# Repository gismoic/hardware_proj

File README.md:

These are all hardware projects I've done over the years, these designs taught me the basics of schematic design and PCB design. Here are some descriptions on each project

# FLAT_MOBO

This project was an attempt at creating a MP3 player design. This project made use of vs1053b codec chip that would take audio data streamed to it via a SPI connection and output a analog audio signal to speakers, the chip could also be used in conjunction with a external microcontroller for addiotional features. This project was a predessor to OTTO, a project that I would persue on later that shared a simiar theroy of operation.

# PIPBOY

this project was an attempt to redesign a gameboy with a Z80 computer instead of it's original hardware. This project also made use of a prototype gameboy emulator that I wanted to build to help me understand the hardware better. Here's a schematic that includes the computer's data and address bus connected to a sram package and a custom prehphrial that would act as a simulated cartridge.

# SD_P

A microSD card breakout board, a way to tinker with a SD card using hardware of my own desgin. A BOM was constructed detailing all parts, cost of each part, and links where to get them. Overall a very simple project.

# BB_PS (battery charger) [WIP]

A custom battery charger design that a uses a cc-cv circuit and a buck regulator for charging batteries. I hope to be able to add a microcontroller that monitors battery percentage and potentially other features. For now it is incomplete

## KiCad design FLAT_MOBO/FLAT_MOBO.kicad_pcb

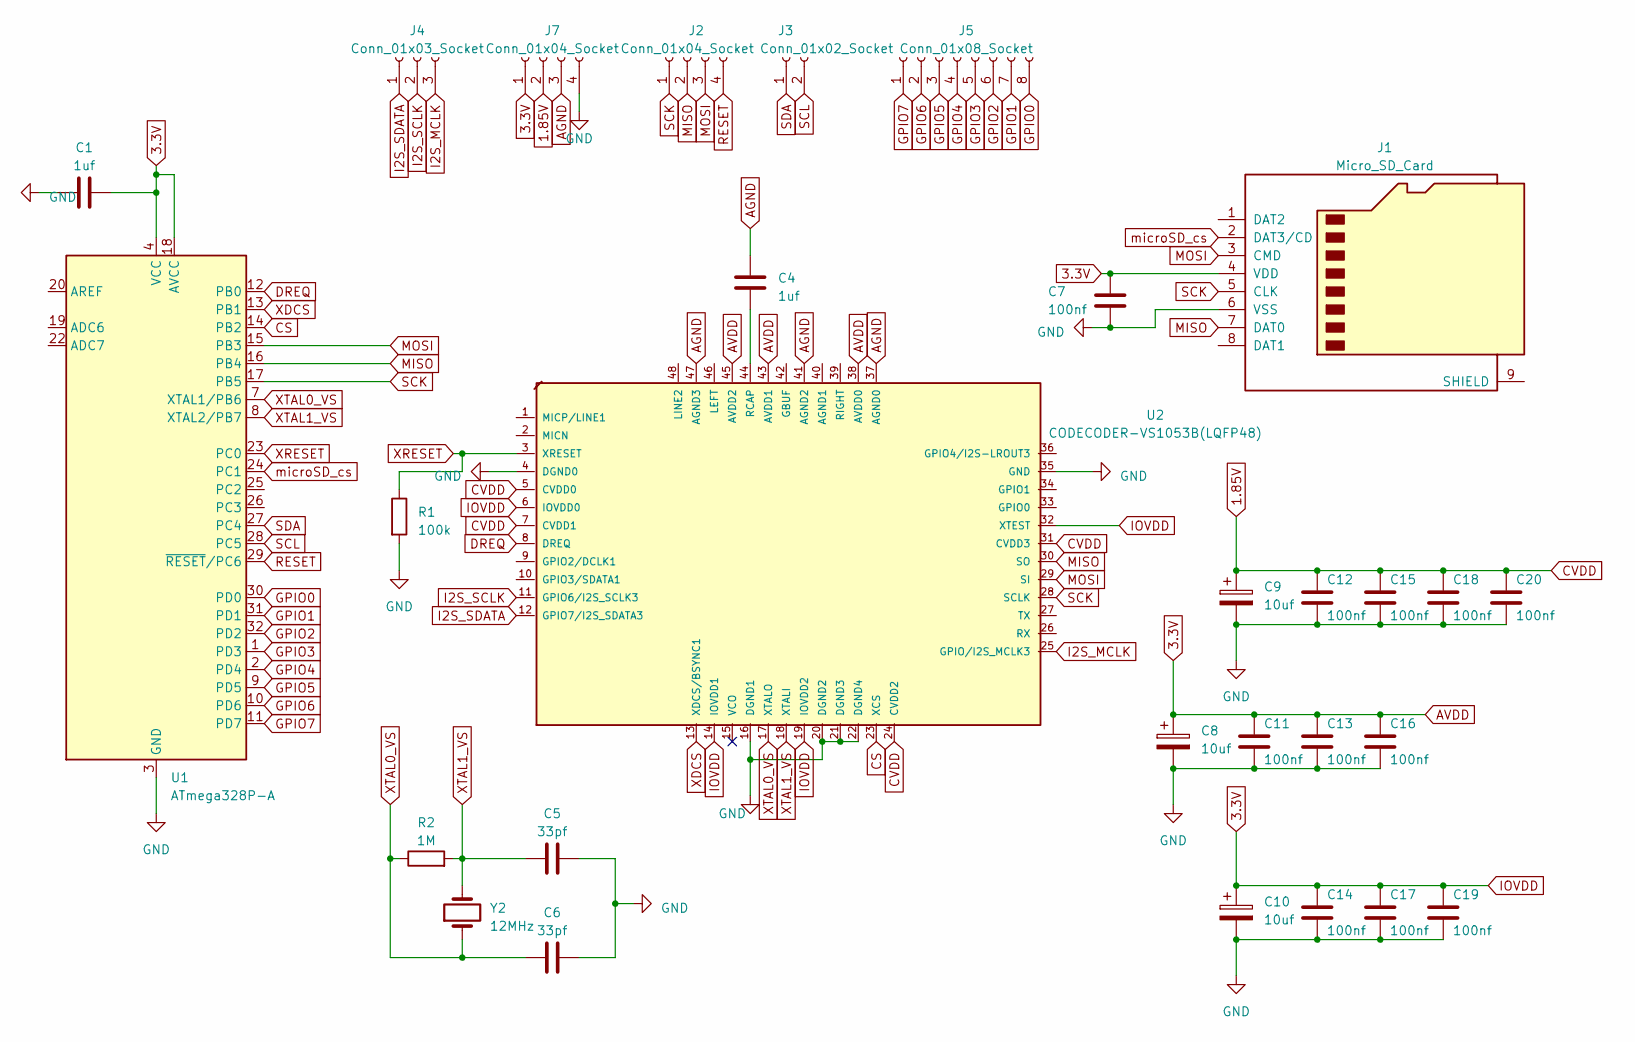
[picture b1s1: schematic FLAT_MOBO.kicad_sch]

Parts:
C1, C4: 1uf; C_0603_1608Metric_Pad1.08x0.95mm_HandSolder
C5, C6: 33pf; C_0603_1608Metric_Pad1.08x0.95mm_HandSolder
C7, C11, C12, C13, C14, C15, C16, C17, C18, C19, C20: 100nf; C_0603_1608Metric_Pad1.08x0.95mm_HandSolder
C8, C9, C10: 10uf; CP_Elec_4x3
J1: Micro_SD_Card; microSD_HC_Hirose_DM3D-SF
J2, J7: Conn_01x04_Socket; PinHeader_1x04_P1.27mm_Vertical
J3: Conn_01x02_Socket; PinHeader_1x02_P1.27mm_Vertical
J4: Conn_01x03_Socket; PinHeader_1x03_P1.27mm_Vertical
J5: Conn_01x08_Socket; PinHeader_1x08_P1.27mm_Vertical
R1: 100k; R_0603_1608Metric_Pad0.98x0.95mm_HandSolder
R2: 1M; R_0603_1608Metric_Pad0.98x0.95mm_HandSolder
U1: ATmega328P-A; TQFP-32_7x7mm_P0.8mm
U2: CODECODER-VS1053B(LQFP48); LQFP-48_7x7mm_P0.5mm; MPN VS1053B
Y2: 12MHz; Crystal_HC49-4H_Vertical

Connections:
1.85V: C9.1, C12.1, C15.1, C18.1, C20.1, J7.2, U2.5 (CVDD0), U2.7 (CVDD1), U2.24 (CVDD2), U2.31 (CVDD3)
3.3V: C1.2, C7.1, C8.1, C10.1, C11.1, C13.1, C14.1, C16.1, C17.1, C19.1, J1.4 (VDD), J7.1, U1.4 (VCC), U1.6 (VCC), U1.18 (AVCC), U2.6 (IOVDD0), U2.14 (IOVDD1), U2.19 (IOVDD2), U2.32 (XTEST), U2.38 (AVDD0), U2.43 (AVDD1), U2.45 (AVDD2)
AGND: C4.1, J7.3, U2.37 (AGND0), U2.41 (AGND2), U2.47 (AGND3)
CS: U1.14 (PB2), U2.23 (XCS)
DREQ: U1.12 (PB0), U2.8 (DREQ)
GND: C1.1, C5.2, C6.2, C7.2, C8.2, C9.2, C10.2, C11.2, C12.2, C13.2, C14.2, C15.2, C16.2, C17.2, C18.2, C19.2, C20.2, J1.6 (VSS), J7.4, R1.2, U1.3 (GND), U1.5 (GND), U1.21 (GND), U2.4 (DGND0), U2.16 (DGND1), U2.20 (DGND2), U2.21 (DGND3), U2.22 (DGND4), U2.35 (GND)
GPIO0: J5.8, U1.30 (PD0)
GPIO1: J5.7, U1.31 (PD1)
GPIO2: J5.6, U1.32 (PD2)
GPIO3: J5.5, U1.1 (PD3)
GPIO4: J5.4, U1.2 (PD4)
GPIO5: J5.3, U1.9 (PD5)
GPIO6: J5.2, U1.10 (PD6)
GPIO7: J5.1, U1.11 (PD7)
I2S_MCLK: J4.3, U2.25 (GPIO/I2S_MCLK3)
I2S_SCLK: J4.2, U2.11 (GPIO6/I2S_SCLK3)
I2S_SDATA: J4.1, U2.12 (GPIO7/I2S_SDATA3)
MISO: J1.7 (DAT0), J2.2, U1.16 (PB4), U2.30 (SO)
MOSI: J1.3 (CMD), J2.3, U1.15 (PB3), U2.29 (SI)
unnamed: C4.2, U2.44 (RCAP)
RESET: J2.4, U1.29 (~RESET/PC6)
SCK: J1.5 (CLK), J2.1, U1.17 (PB5), U2.28 (SCLK)
SCL: J3.2, U1.28 (PC5)
SDA: J3.1, U1.27 (PC4)
XDCS: U1.13 (PB1), U2.13 (XDCS/BSYNC1)
XRESET: R1.1, U1.23 (PC0), U2.3 (XRESET)
XTAL0_VS: C6.1, R2.1, U1.7 (XTAL1/PB6), U2.17 (XTALO), Y2.1
XTAL1_VS: C5.1, R2.2, U1.8 (XTAL2/PB7), U2.18 (XTALI), Y2.2
microSD_cs: J1.2 (DAT3/CD), U1.24 (PC1)
sCS: U1.25 (PC2)

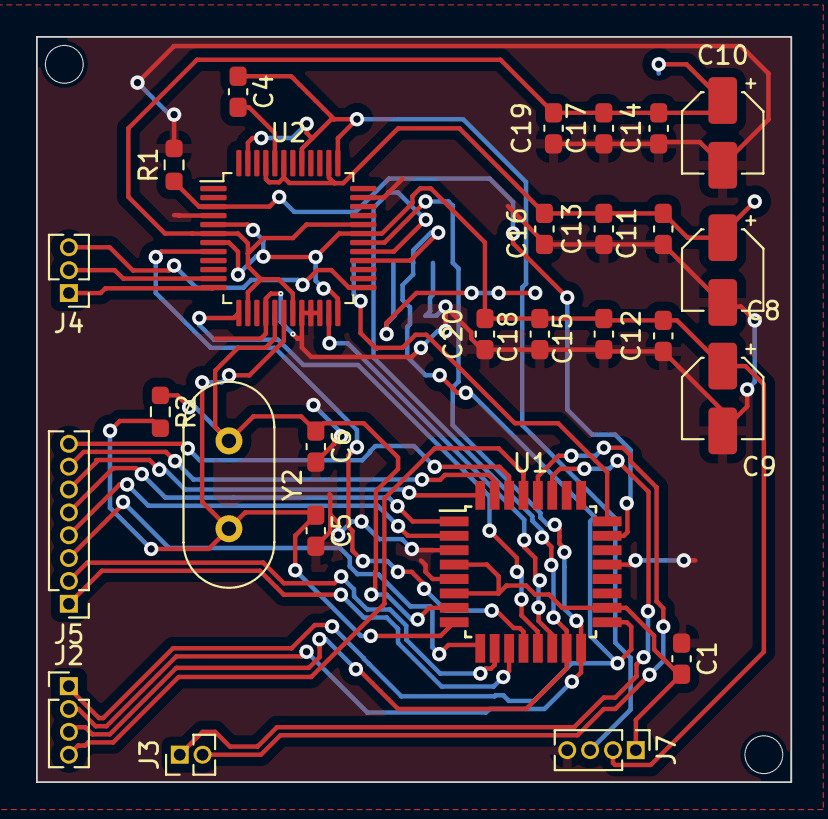
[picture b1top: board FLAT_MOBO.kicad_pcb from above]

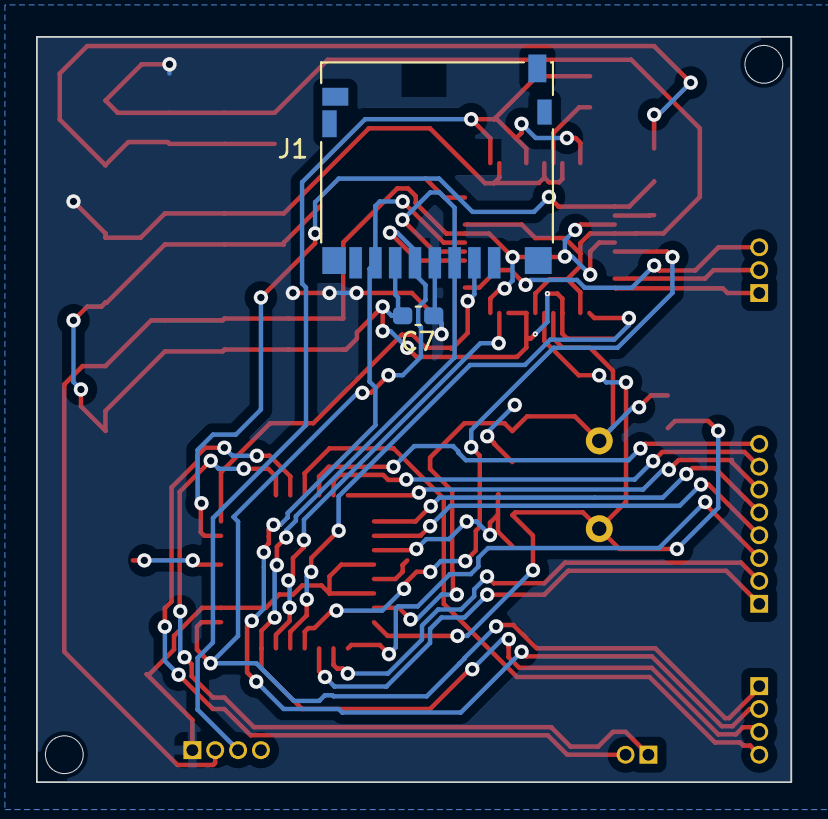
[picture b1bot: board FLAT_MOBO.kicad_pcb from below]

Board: 2 copper layers, 41.9 x 41.4 mm, 29 parts (2 on the bottom side), 29 nets.

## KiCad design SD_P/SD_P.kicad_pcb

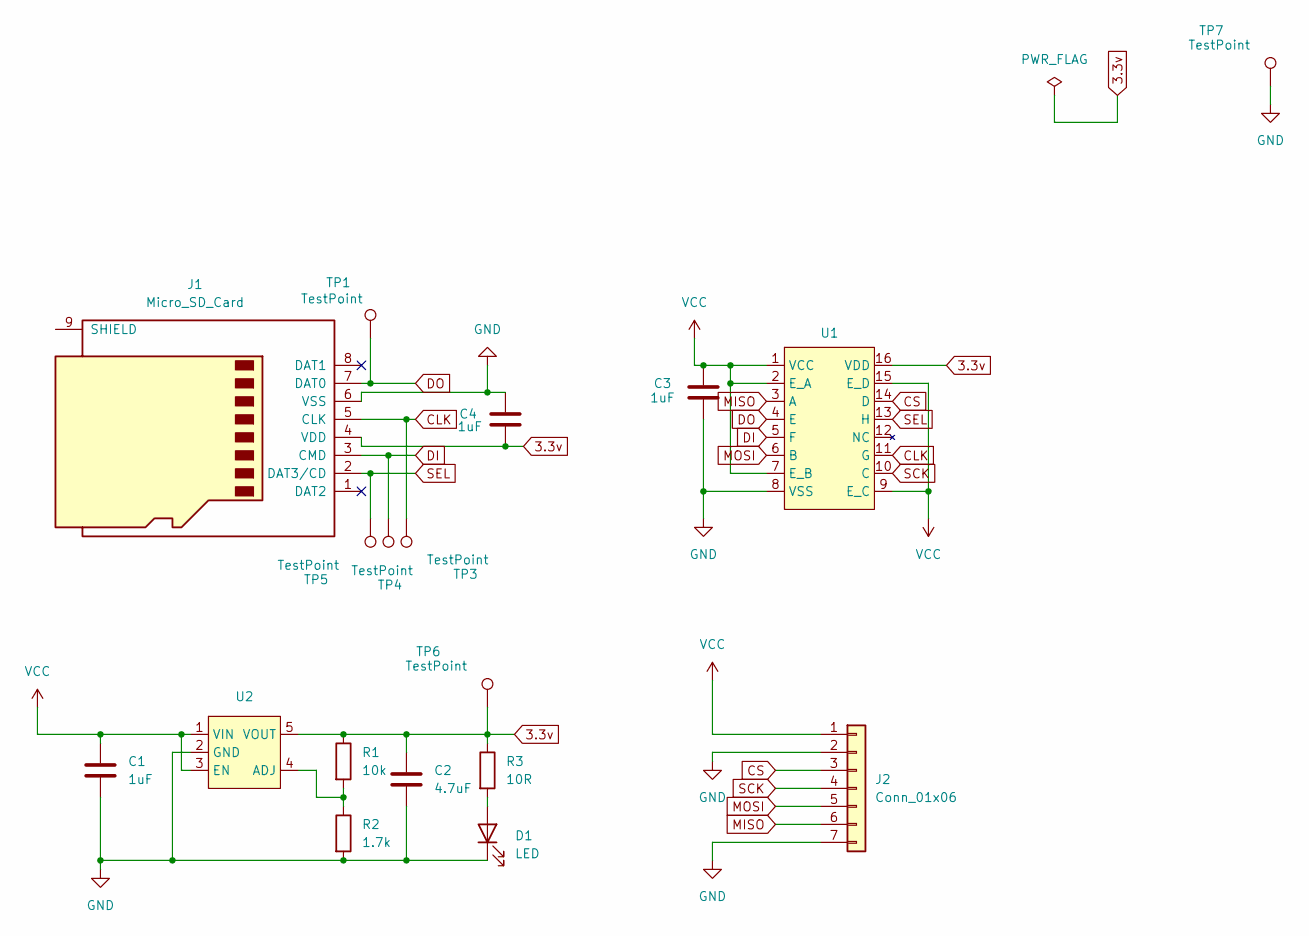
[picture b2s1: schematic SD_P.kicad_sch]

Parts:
C1, C3, C4: 1uF; C_0603_1608Metric_Pad1.08x0.95mm_HandSolder
C2: 4.7uF; C_0603_1608Metric_Pad1.08x0.95mm_HandSolder
D1: LED; LED_0603_1608Metric_Pad1.05x0.95mm_HandSolder
J1: Micro_SD_Card; microSD_HC_Hirose_DM3D-SF
J2: Conn_01x06; PinHeader_1x07_P2.54mm_Vertical
R1: 10k; R_0603_1608Metric_Pad0.98x0.95mm_HandSolder
R2: 1.7k; R_0603_1608Metric_Pad0.98x0.95mm_HandSolder
R3: 10R; R_0603_1608Metric_Pad0.98x0.95mm_HandSolder
TP1, TP3, TP4, TP5, TP6, TP7: TestPoint; TestPoint_Pad_D1.0mm
U1: TSSOP-16_4.4x5mm_P0.65mm
U2: TSOT-23-5_HandSoldering

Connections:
3.3v: C2.1, C4.2, J1.4 (VDD), R1.1, R3.1, TP6.1, U1.16 (VDD), U2.5 (VOUT)
CLK: J1.5 (CLK), TP3.1, U1.11 (G)
CS: J2.3, U1.14 (D)
DI: J1.3 (CMD), TP4.1, U1.5 (F)
DO: J1.7 (DAT0), TP1.1, U1.4 (E)
GND: C1.2, C2.2, C3.2, C4.1, D1.1 (K), J1.6 (VSS), J2.2, J2.7, R2.2, TP7.1, U1.8 (VSS), U2.2 (GND)
MISO: J2.6, U1.3 (A)
MOSI: J2.5, U1.6 (B)
unnamed: D1.2 (A), R3.2
unnamed: R1.2, R2.1, U2.4 (ADJ)
SCK: J2.4, U1.10 (C)
SEL: J1.2 (DAT3/CD), TP5.1, U1.13 (H)
VCC: C1.1, C3.1, J2.1, U1.1 (VCC), U1.2 (E_A), U1.7 (E_B), U1.9 (E_C), U1.15 (E_D), U2.1 (VIN), U2.3 (EN)

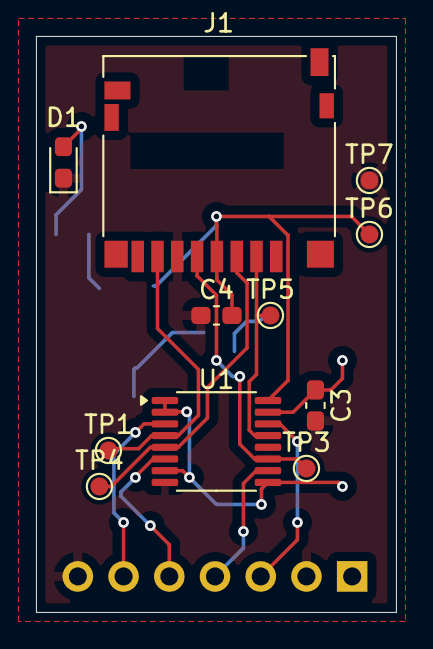
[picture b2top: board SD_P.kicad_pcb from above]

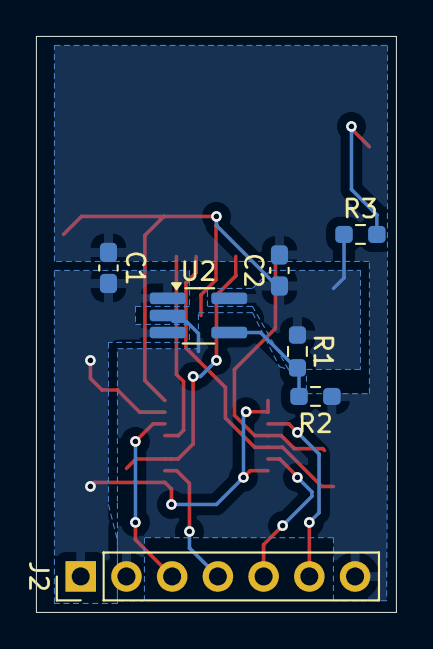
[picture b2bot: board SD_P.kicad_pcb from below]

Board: 2 copper layers, 20.0 x 32.0 mm, 18 parts (7 on the bottom side), 13 nets.
